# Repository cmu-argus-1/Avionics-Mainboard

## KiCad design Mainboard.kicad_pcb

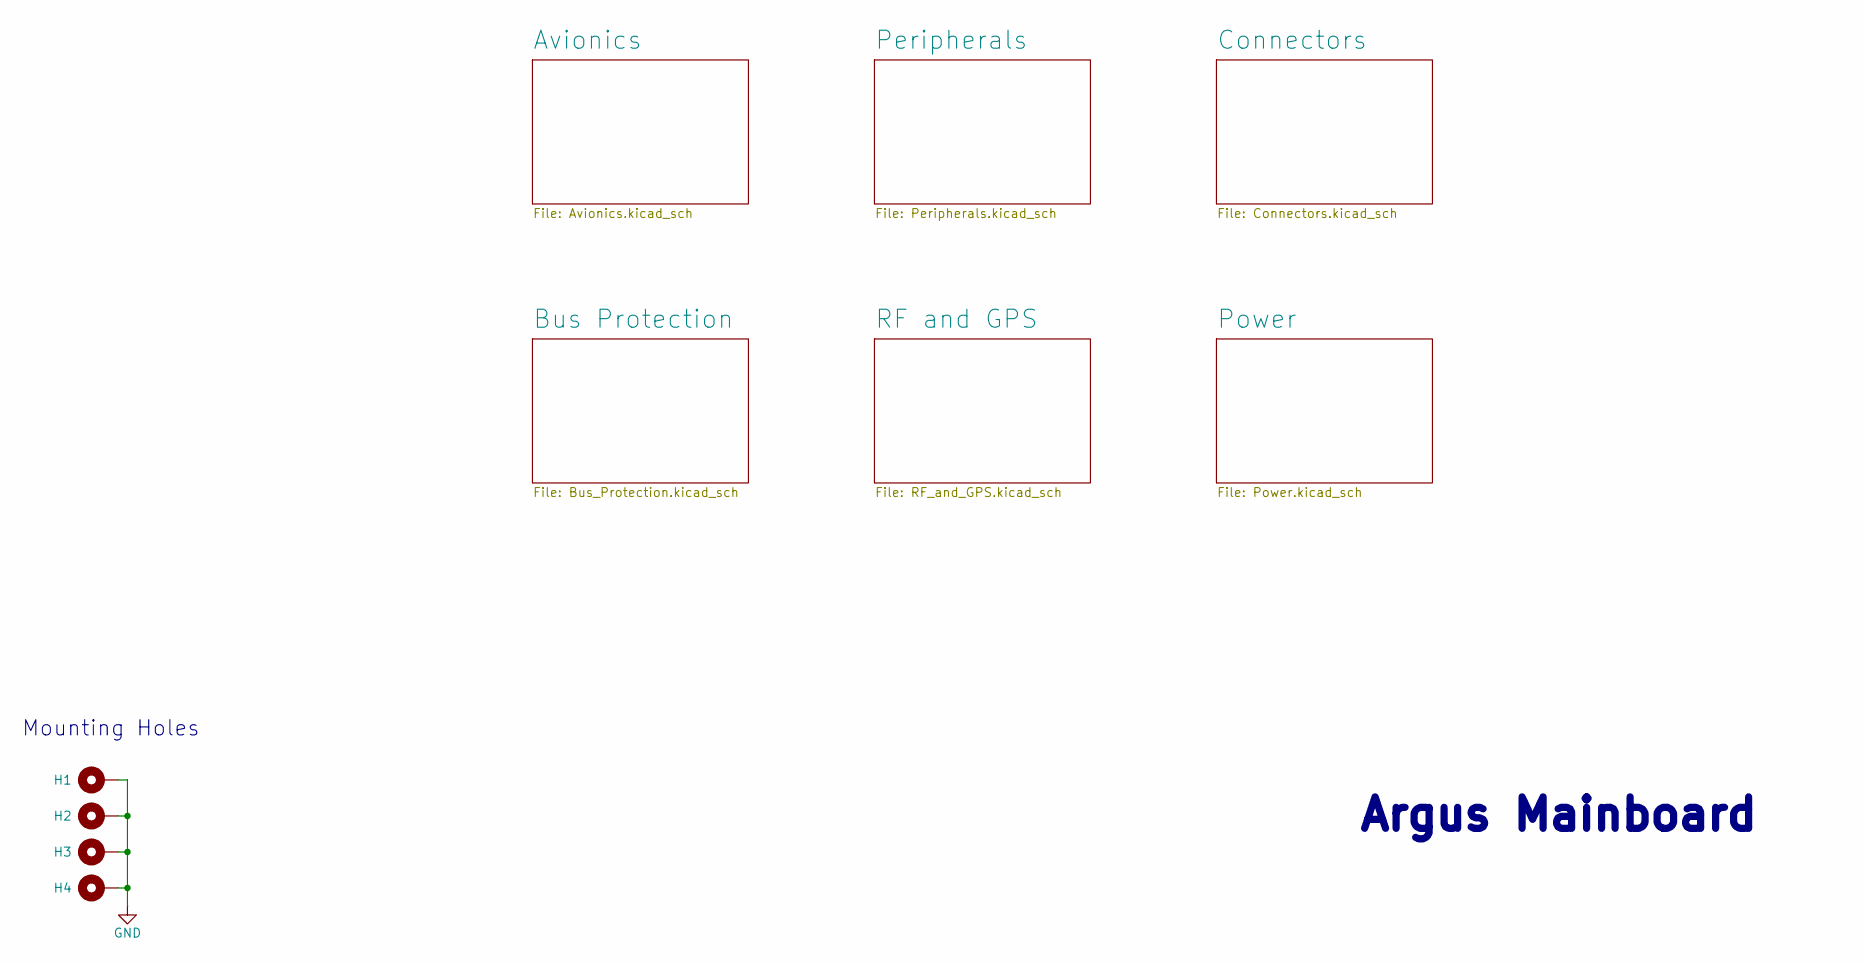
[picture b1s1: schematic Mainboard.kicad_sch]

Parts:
H1, H2, H3, H4: MountingHole_Pad; MountingHole2

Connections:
GND: H1.1, H2.1, H3.1, H4.1; also elsewhere on the board

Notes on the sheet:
Mounting Holes
Argus Mainboard

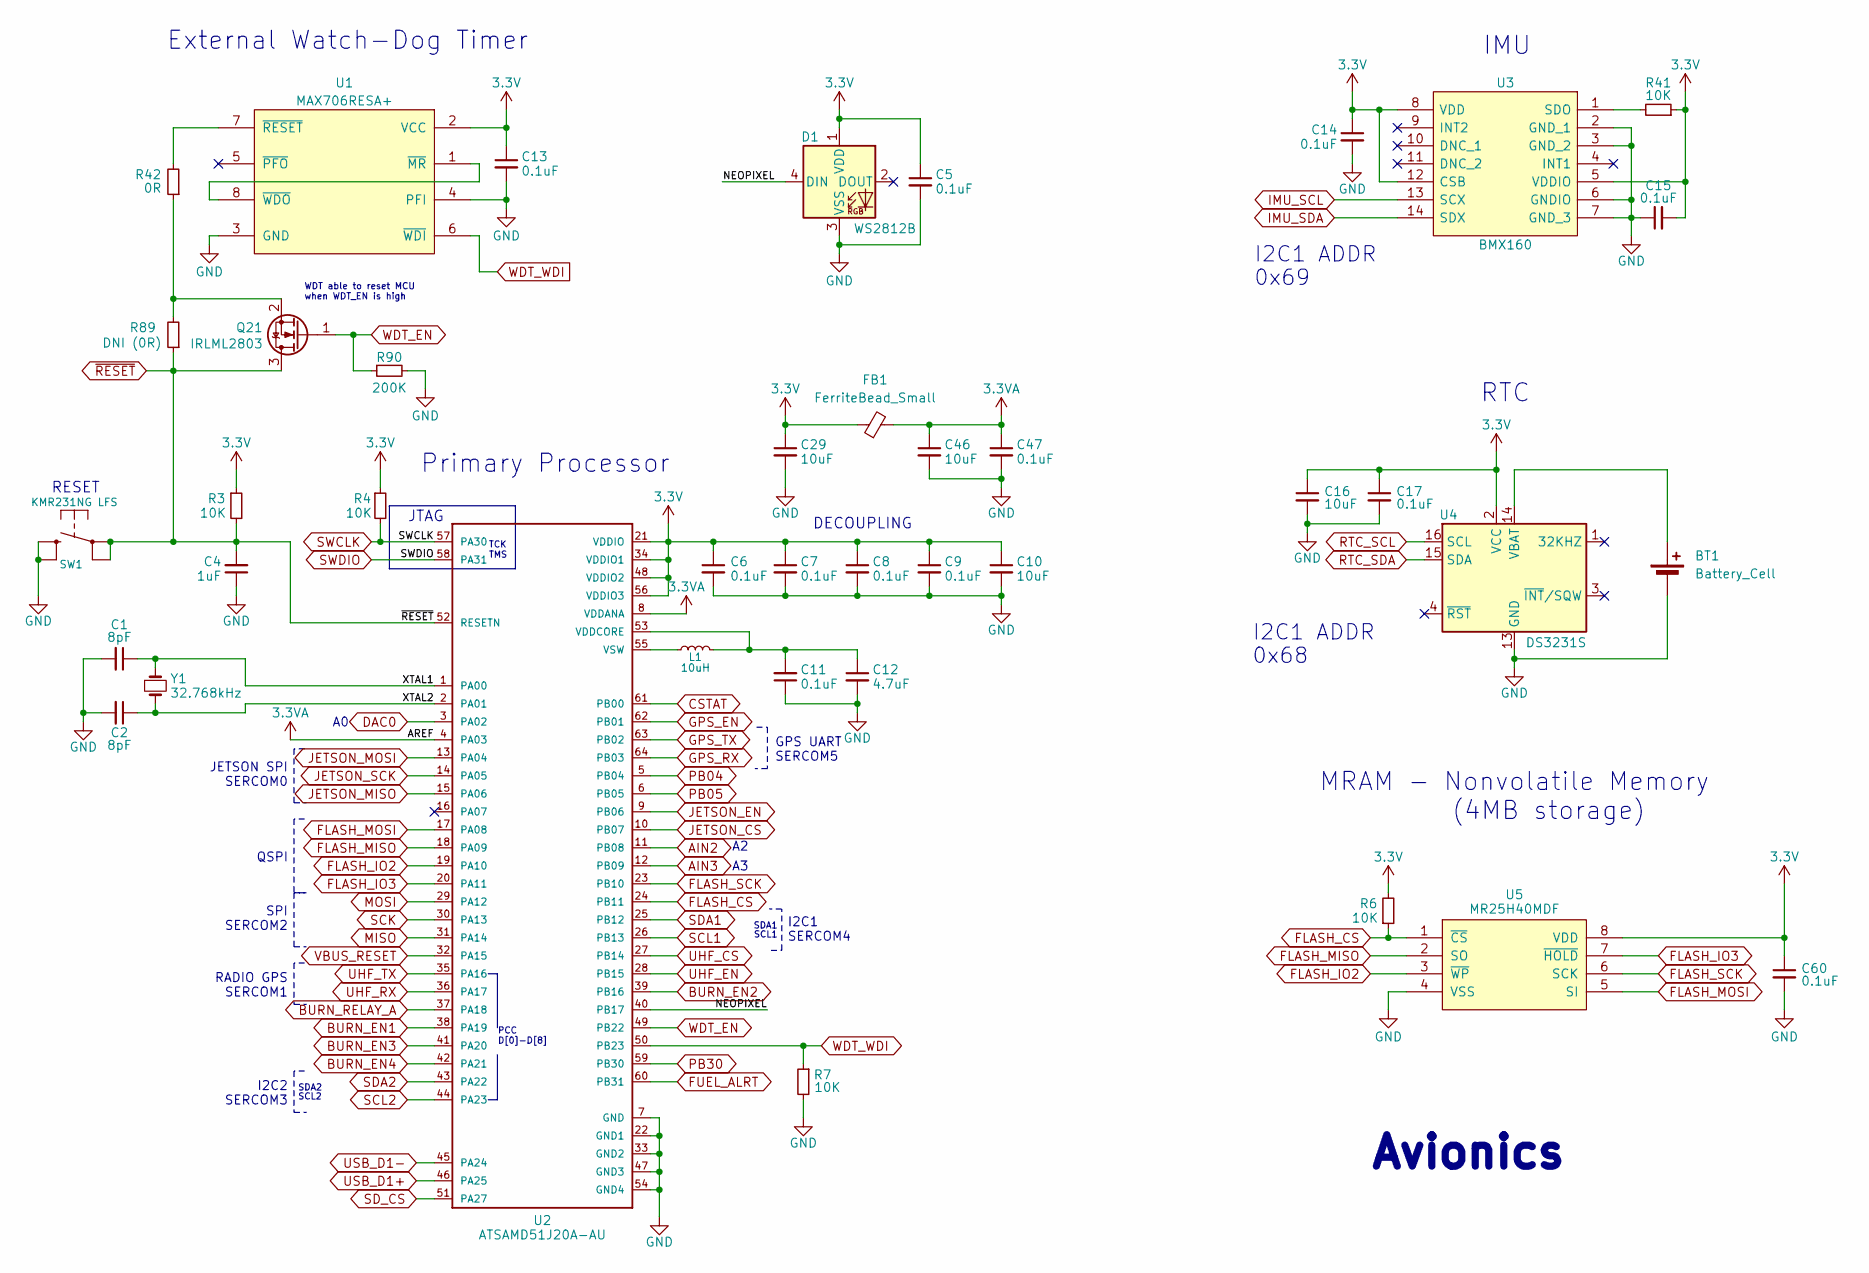
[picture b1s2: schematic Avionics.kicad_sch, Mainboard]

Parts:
BT1: Battery_Cell; BatteryHolder_LINX_BAT-HLD-012-SMT
C1, C2: 8pF; C_0603_1608Metric
C4: 1uF; C_0603_1608Metric
C5, C6, C7, C8, C9, C11, C13, C14, C15, C17, C47, C60: 0.1uF; C_0603_1608Metric
C10, C16, C29, C46: 10uF; C_0603_1608Metric
C12: 4.7uF; C_0603_1608Metric
D1: WS2812B; LED_WS2812B_PLCC4_5.0x5.0mm_P3.2mm; Manufacturer_Part_Number WS2812B-B
FB1: FerriteBead_Small; L_0603_1608Metric
L1: 10uH; L_0805_2012Metric_Pad1.15x1.40mm_HandSolder; Manufacturer_Part_Number MGFL2012F100MT-LF
Q21: IRLML2803; SOT-23
R3, R4, R6, R7, R41: 10K; R_0603_1608Metric
R42: 0R; R_0603_1608Metric
R89: DNI (0R); R_0603_1608Metric
R90: 200K; R_0603_1608Metric
SW1: KMR231NG LFS; SW_Push_1P1T_NO_CK_KMR2; Manufacturer_Part_Number KMR231NG LFS
U1: MAX706RESA+; SOIC-8_3.9x4.9mm_P1.27mm
U2: ATSAMD51J20A-AU; TQFP-64_10x10mm_P0.5mm; Manufacturer_Part_Number ATSAMD51J20A-AU
U3: BMX160; Bosch_LGA-14_3x2.5mm_P0.5mm; Manufacturer_Part_Number BMX160
U4: DS3231S; SOIC-16W_7.5x10.3mm_P1.27mm
U5: MR25H40MDF; DFN-8-1EP_6x5mm_P1.27mm_EP2x2mm; Manufacturer_Part_Number W25Q80DVSNIG
Y1: 32.768kHz; Crystal_SMD_3215-2Pin_3.2x1.5mm; Manufacturer_Part_Number SC-32S32.768kHz20PPM7pF

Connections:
3.3V: C5.1, C6.1, C7.1, C8.1, C9.1, C10.1, C13.1, C14.1, C15.2, C16.1, C17.1, C29.1, C60.1, D1.1 (VDD), FB1.1, R3.1, R4.1, R6.2, R41.1, U1.2 (VCC), U2.21 (VDDIO), U2.34 (VDDIO1), U2.48 (VDDIO2), U2.56 (VDDIO3), U3.5 (VDDIO), U3.8 (VDD), U3.12 (CSB), U4.2 (VCC), U5.8 (VDD); also elsewhere on the board
3.3VA: C46.1, C47.1, FB1.2, U2.4 (PA03), U2.8 (VDDANA)
/Avionics/NEOPIXEL: D1.4 (DIN), U2.40 (PB17)
/Avionics/XTAL1: C1.1, U2.1 (PA00), Y1.1
/Avionics/XTAL2: C2.1, U2.2 (PA01), Y1.2
AIN2: U2.11 (PB08); also elsewhere on the board
AIN3: U2.12 (PB09)
BURN_EN1: U2.38 (PA19); also elsewhere on the board
BURN_EN2: U2.39 (PB16); also elsewhere on the board
BURN_EN3: U2.41 (PA20); also elsewhere on the board
BURN_EN4: U2.42 (PA21); also elsewhere on the board
BURN_RELAY_A: U2.37 (PA18); also elsewhere on the board
CSTAT: U2.61 (PB00); also elsewhere on the board
DAC0: U2.3 (PA02); also elsewhere on the board
FLASH_CS: R6.1, U2.24 (PB11), U5.1 (~CS)
FLASH_IO2: U2.19 (PA10), U5.3 (~WP)
FLASH_IO3: U2.20 (PA11), U5.7 (~HOLD)
FLASH_MISO: U2.18 (PA09), U5.2 (SO)
FLASH_MOSI: U2.17 (PA08), U5.5 (SI)
FLASH_SCK: U2.23 (PB10), U5.6 (SCK)
FUEL_ALRT: U2.60 (PB31); also elsewhere on the board
GND: BT1.2 (-), C1.2, C2.2, C4.1, C5.2, C6.2, C7.2, C8.2, C9.2, C10.2, C11.1, C12.2, C13.2, C14.2, C15.1, C16.2, C17.2, C29.2, C46.2, C47.2, C60.2, D1.3 (VSS), R7.2, R90.2, SW1.2 (S), U1.3 (GND), U1.4 (PFI), U2.7 (GND), U2.22 (GND1), U2.33 (GND2), U2.47 (GND3), U2.54 (GND4), U3.2 (GND_1), U3.3 (GND_2), U3.6 (GNDIO), U3.7 (GND_3), U4.5 (GND), U4.6 (GND), U4.7 (GND), U4.8 (GND), U4.9 (GND), U4.10 (GND), U4.11 (GND), U4.12 (GND), U4.13 (GND), U5.4 (VSS), U5.9 (EP); also elsewhere on the board
GPS_EN: U2.62 (PB01); also elsewhere on the board
GPS_RX: U2.64 (PB03); also elsewhere on the board
GPS_TX: U2.63 (PB02); also elsewhere on the board
IMU_SCL: U3.13 (SCX); also elsewhere on the board
IMU_SDA: U3.14 (SDX); also elsewhere on the board
JETSON_CS: U2.10 (PB07); also elsewhere on the board
JETSON_EN: U2.9 (PB06); also elsewhere on the board
JETSON_MISO: U2.15 (PA06); also elsewhere on the board
JETSON_MOSI: U2.13 (PA04); also elsewhere on the board
JETSON_SCK: U2.14 (PA05); also elsewhere on the board
MISO: U2.31 (PA14); also elsewhere on the board
MOSI: U2.29 (PA12); also elsewhere on the board
unnamed: BT1.1 (+), U4.14 (VBAT)
unnamed: Q21.2 (S), R42.1, R89.2
unnamed: U1.1 (~MR), U1.8 (~WDO)
unnamed: R42.2, U1.7 (~RESET)
unnamed: C11.2, C12.1, L1.1, U2.53 (VDDCORE)
unnamed: L1.2, U2.55 (VSW)
unnamed: R41.2, U3.1 (SDO)
PB04: U2.5 (PB04); also elsewhere on the board
PB05: U2.6 (PB05); also elsewhere on the board
PB30: U2.59 (PB30); also elsewhere on the board
RTC_SCL: U4.16 (SCL); also elsewhere on the board
RTC_SDA: U4.15 (SDA); also elsewhere on the board
SCK: U2.30 (PA13); also elsewhere on the board
SCL1: U2.26 (PB13); also elsewhere on the board
SCL2: U2.44 (PA23); also elsewhere on the board
SDA1: U2.25 (PB12); also elsewhere on the board
SDA2: U2.43 (PA22); also elsewhere on the board
SD_CS: U2.51 (PA27); also elsewhere on the board
SWCLK: R4.2, U2.57 (PA30); also elsewhere on the board
SWDIO: U2.58 (PA31); also elsewhere on the board
UHF_CS: U2.27 (PB14); also elsewhere on the board
UHF_EN: U2.28 (PB15); also elsewhere on the board
UHF_RX: U2.36 (PA17); also elsewhere on the board
UHF_TX: U2.35 (PA16); also elsewhere on the board
USB_D1+: U2.46 (PA25); also elsewhere on the board
USB_D1-: U2.45 (PA24); also elsewhere on the board
VBUS_RESET: U2.32 (PA15); also elsewhere on the board
WDT_EN: Q21.1 (G), R90.1, U2.49 (PB22)
WDT_WDI: R7.1, U1.6 (~WDI), U2.50 (PB23)
~RESET: C4.2, Q21.3 (D), R3.2, R89.1, SW1.1, U2.52 (RESETN); also elsewhere on the board

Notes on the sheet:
RTC
RADIO GPS SERCOM1
SDA2
Primary Processor
SCL2
I2C1 ADDR
0x69
GPS UART SERCOM5
IMU
I2C1 SERCOM4
SPI SERCOM2
RESET
WDT able to reset MCU when WDT_EN is high
JETSON SPI SERCOM0
0x68
Avionics
SDA1
SCL1
TCK TMS
QSPI
External Watch-Dog Timer
I2C2 SERCOM3
PCC D[0]-D[8]
JTAG
DECOUPLING
MRAM - Nonvolatile Memory (4MB storage)

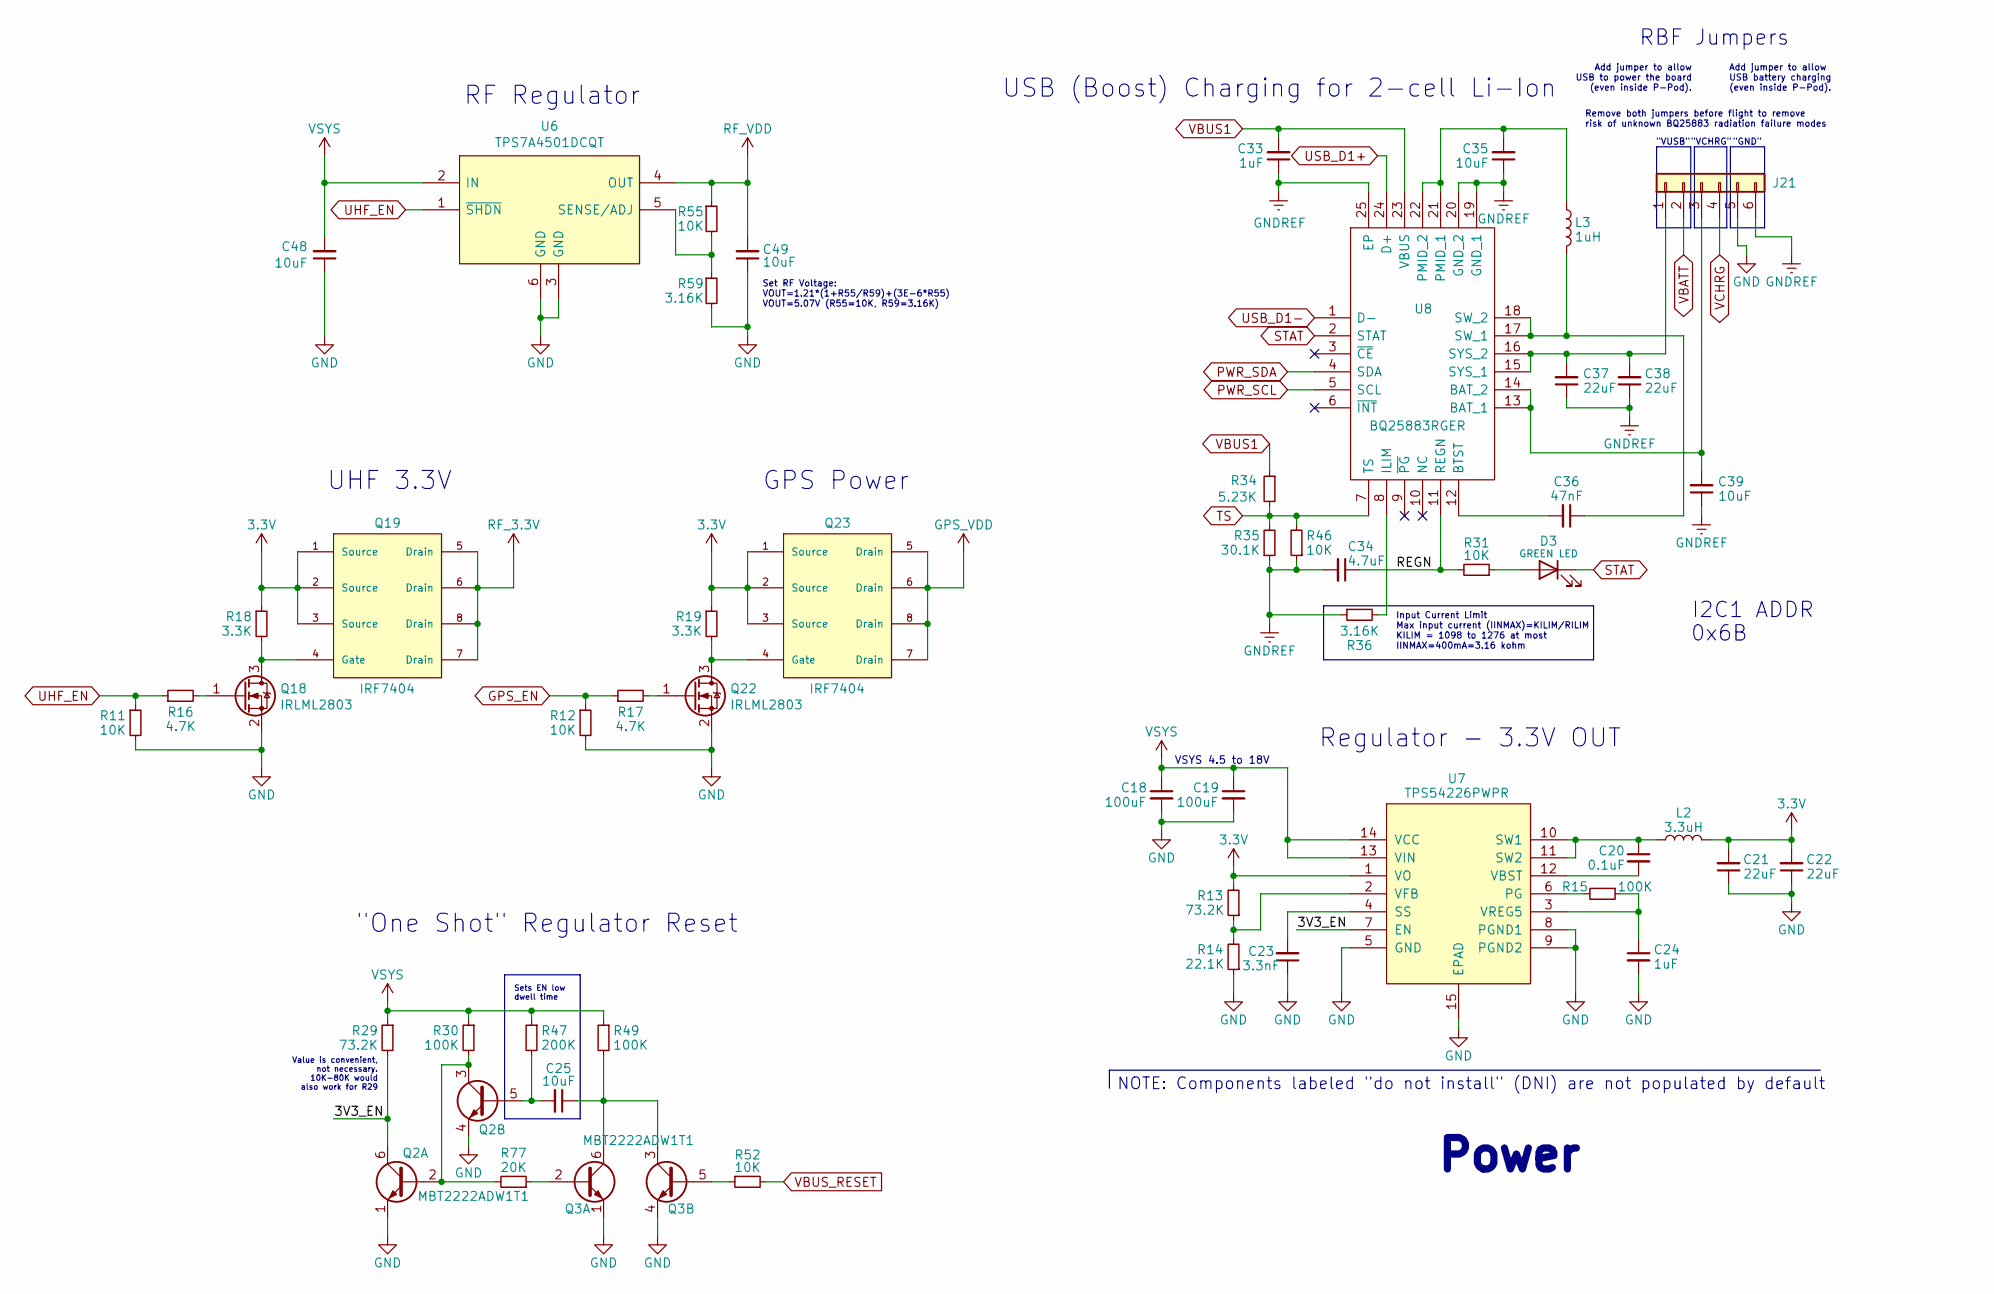
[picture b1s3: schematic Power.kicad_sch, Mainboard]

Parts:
C18, C19: 100uF; C_0805_2012Metric
C20: 0.1uF; C_0603_1608Metric
C21, C22, C37, C38: 22uF; C_0603_1608Metric
C23: 3.3nF; C_0603_1608Metric
C24, C33: 1uF; C_0603_1608Metric
C25, C35, C39, C48, C49: 10uF; C_0603_1608Metric
C34: 4.7uF; C_0603_1608Metric
C36: 47nF; C_0603_1608Metric
D3: GREEN LED; LED_0603_1608Metric; Manufacturer_Part_Number LTST-C190KGKT
J21: Conn_01x06; PinHeader_1x06_P2.54mm_Vertical
L2: 3.3uH; L_1812_4532Metric; Manufacturer_Part_Number HPC5040NF-3R3MTH
L3: 1uH; L_Wuerth_MAPI-2510; Manufacturer_Part_Number MCS25GD-1R0MMP
Q2, Q3: MBT2222ADW1T1; SOT-363_SC-70-6; Manufacturer_Part_Number MBT2222ADW1T1G
Q18, Q22: IRLML2803; SOT-23
Q19, Q23: IRF7404; SOIC-8_3.9x4.9mm_P1.27mm; Manufacturer_Part_Number NDS8434
R11, R12, R31, R46, R52, R55: 10K; R_0603_1608Metric
R13, R29: 73.2K; R_0603_1608Metric
R14: 22.1K; R_0603_1608Metric
R15, R30, R49: 100K; R_0603_1608Metric
R16, R17: 4.7K; R_0603_1608Metric
R18, R19: 3.3K; R_0603_1608Metric
R34: 5.23K; R_0603_1608Metric
R35: 30.1K; R_0603_1608Metric
R36, R59: 3.16K; R_0603_1608Metric
R47: 200K; R_0603_1608Metric
R77: 20K; R_0603_1608Metric
U6: TPS7A4501DCQT; SOT-223-6; Manufacturer_Part_Number TPS7A4501DCQT
U7: TPS54226PWPR; HTSSOP-14-1EP_4.4x5mm_P0.65mm_EP3.4x5mm_Mask3x3.1mm; Manufacturer_Part_Number TPS54226PWPR
U8: BQ25883RGER; Texas_RGE0024H_VQFN-24-1EP_4x4mm_P0.5mm_EP2.7x2.7mm; Manufacturer_Part_Number BQ25883RGER

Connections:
3.3V: C21.2, C22.2, L2.2, Q19.1 (Source), Q19.2 (Source), Q19.3 (Source), Q23.1 (Source), Q23.2 (Source), Q23.3 (Source), R13.2, R18.1, R19.1, U7.1 (VO); also elsewhere on the board
/Power/3V3_EN: Q2.6 (C1), R29.2, U7.7 (EN)
/Power/REGN: C34.1, R31.2, U8.11 (REGN)
GND: C18.2, C19.2, C21.1, C22.1, C23.1, C24.2, C48.1, C49.1, J21.5, Q2.1 (E1), Q2.4 (E2), Q3.1 (E1), Q3.4 (E2), Q18.2 (S), Q22.2 (S), R11.2, R12.2, R14.1, R59.2, U6.3 (GND), U6.6 (GND), U7.5 (GND), U7.8 (PGND1), U7.9 (PGND2), U7.15 (EPAD); also elsewhere on the board
GNDREF: C33.1, C34.2, C35.1, C37.1, C38.1, C39.1, J21.6, R35.1, R36.1, R46.1, U8.19 (GND_1), U8.20 (GND_2), U8.25 (EP); also elsewhere on the board
GPS_EN: R12.1, R17.1; also elsewhere on the board
GPS_VDD: Q23.5 (Drain), Q23.6 (Drain), Q23.7 (Drain), Q23.8 (Drain); also elsewhere on the board
unnamed: D3.2 (A), R31.1
unnamed: C37.2, C38.2, J21.1, U8.15 (SYS_1), U8.16 (SYS_2)
unnamed: C39.2, J21.3, U8.13 (BAT_1), U8.14 (BAT_2)
unnamed: Q2.2 (B1), Q2.3 (C2), R30.2, R77.2
unnamed: C25.2, Q2.5 (B2), R47.2
unnamed: Q3.2 (B1), R77.1
unnamed: C25.1, Q3.3 (C2), Q3.6 (C1), R49.2
unnamed: Q3.5 (B2), R52.1
unnamed: Q18.3 (D), Q19.4 (Gate), R18.2
unnamed: Q18.1 (G), R16.2
unnamed: Q22.3 (D), Q23.4 (Gate), R19.2
unnamed: Q22.1 (G), R17.2
unnamed: R55.2, R59.1, U6.5 (SENSE/ADJ)
unnamed: R15.2, U7.6 (PG)
unnamed: C23.2, U7.4 (SS)
unnamed: C20.1, L2.1, U7.10 (SW1), U7.11 (SW2)
unnamed: C20.2, U7.12 (VBST)
unnamed: R13.1, R14.2, U7.2 (VFB)
unnamed: C24.1, R15.1, U7.3 (VREG5)
unnamed: C36.2, U8.12 (BTST)
unnamed: R36.2, U8.8 (ILIM)
unnamed: C35.2, L3.1, U8.21 (PMID_1), U8.22 (PMID_2)
unnamed: C36.1, L3.2, U8.17 (SW_1), U8.18 (SW_2)
PWR_SCL: U8.5 (SCL); also elsewhere on the board
PWR_SDA: U8.4 (SDA); also elsewhere on the board
RF_3.3V: Q19.5 (Drain), Q19.6 (Drain), Q19.7 (Drain), Q19.8 (Drain); also elsewhere on the board
RF_VDD: C49.2, R55.1, U6.4 (OUT); also elsewhere on the board
STAT: D3.1 (K), U8.2 (STAT)
TS: R34.2, R35.2, R46.2, U8.7 (TS)
UHF_EN: R11.1, R16.1, U6.1 (~SHDN); also elsewhere on the board
USB_D1+: U8.24 (D+); also elsewhere on the board
USB_D1-: U8.1 (D-); also elsewhere on the board
VBATT: J21.2; also elsewhere on the board
VBUS1: C33.2, R34.1, U8.23 (VBUS); also elsewhere on the board
VBUS_RESET: R52.2; also elsewhere on the board
VCHRG: J21.4; also elsewhere on the board
VSYS: C18.1, C19.1, C48.2, R29.1, R30.1, R47.1, R49.1, U6.2 (IN), U7.13 (VIN), U7.14 (VCC); also elsewhere on the board

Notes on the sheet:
"VCHRG"
RF Regulator
Sets EN low dwell time
Remove both jumpers before flight to remove risk of unknown BQ25883 radiation failure modes
0x6B
RBF Jumpers
Add jumper to allow USB battery charging (even inside P-Pod).
"One Shot" Regulator Reset
GPS Power
Value is convenient, not necessary. 10K-80K would also work for R29
USB (Boost) Charging for 2-cell Li-Ion
UHF 3.3V
"GND"
VSYS 4.5 to 18V
Input Current Limit Max input current (IINMAX)=KILIM/RILIM KILIM = 1098 to 1276 at most IINMAX=400mA=3.16 kohm
"VUSB"
I2C1 ADDR
Power
Set RF Voltage: VOUT=1.21*(1+R55/R59)+(3E-6*R55) VOUT=5.07V (R55=10K, R59=3.16K)
Regulator - 3.3V OUT
Add jumper to allow USB to power the board (even inside P-Pod).
NOTE: Components labeled "do not install" (DNI) are not populated by default

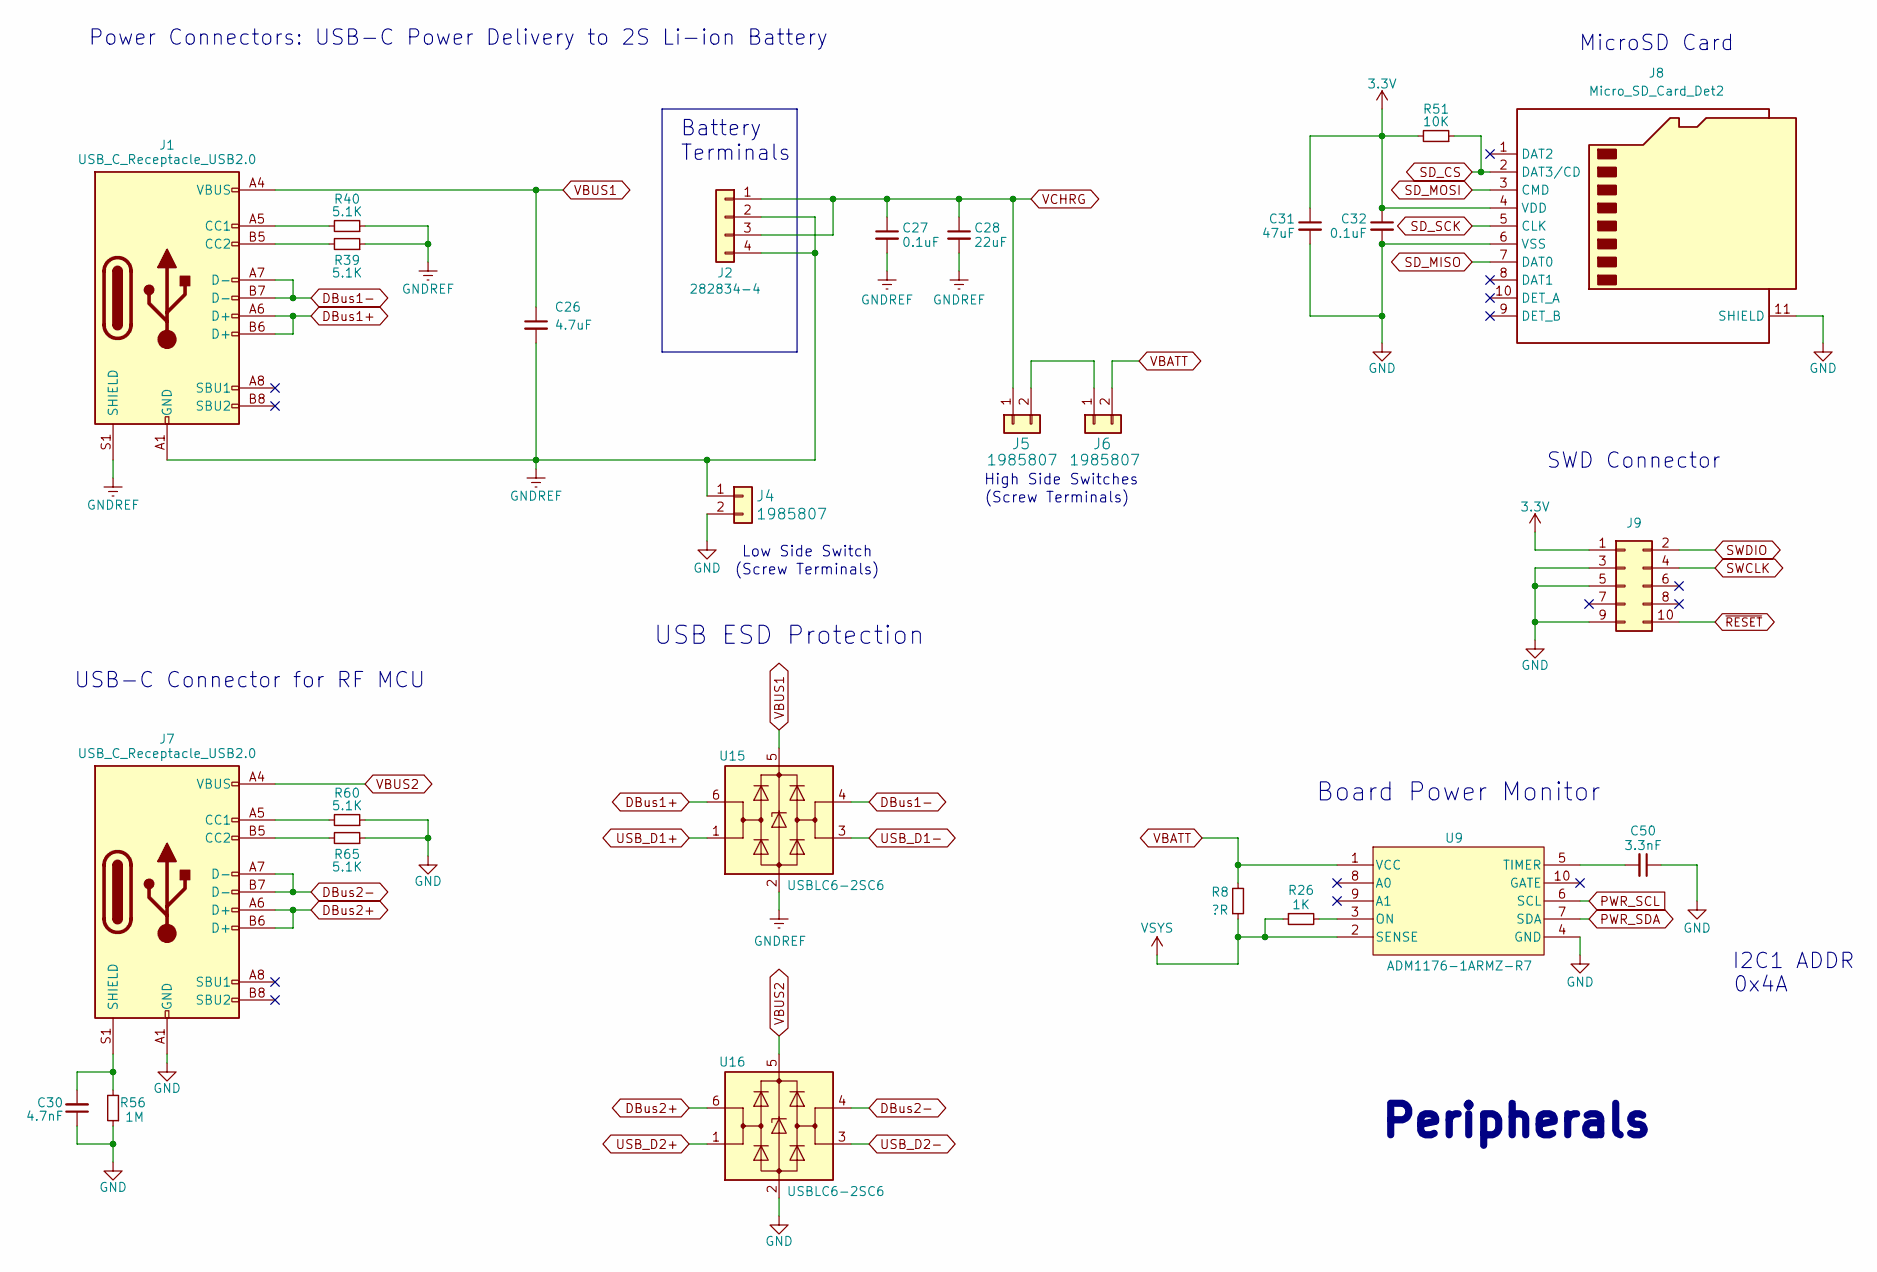
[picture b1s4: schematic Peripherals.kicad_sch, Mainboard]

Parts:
C26: 4.7uF; C_0603_1608Metric
C27, C32: 0.1uF; C_0603_1608Metric
C28: 22uF; C_0603_1608Metric
C30: 4.7nF; C_0603_1608Metric
C31: 47uF; C_0805_2012Metric
C50: 3.3nF; C_0603_1608Metric
J1, J7: USB_C_Receptacle_USB2.0; USB_C_Receptacle_HRO_TYPE-C-31-M-12; Manufacturer_Part_Number U262-161N-4BVC11
J2: 282834-4; TE_282834-4
J4, J5, J6: 1985807; PHOENIX_1985807; Manufacturer_Part_Number 1985807
J8: Micro_SD_Card_Det2; microSD_HC_Molex_104031-0811
J9: Conn_02x05_Odd_Even; PinHeader_2x05_P1.27mm_Vertical_SMD
R8: ?R; R_2512_6332Metric
R26: 1K; R_0603_1608Metric
R39, R40, R60, R65: 5.1K; R_0603_1608Metric
R51: 10K; R_0603_1608Metric
R56: 1M; R_0603_1608Metric
U9: ADM1176-1ARMZ-R7; MSOP-10_3x3mm_P0.5mm; Manufacturer_Part_Number ADM1176-1ARMZ-R7
U15, U16: USBLC6-2SC6; SOT-23-6

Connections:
3.3V: C31.1, C32.1, J8.4 (VDD), J9.1, R51.2; also elsewhere on the board
DBus1+: J1.A6 (D+), J1.B6 (D+), U15.6 (I/O1)
DBus1-: J1.A7 (D-), J1.B7 (D-), U15.4 (I/O2)
DBus2+: J7.A6 (D+), J7.B6 (D+), U16.6 (I/O1)
DBus2-: J7.A7 (D-), J7.B7 (D-), U16.4 (I/O2)
GND: C30.1, C31.2, C32.2, C50.1, J4.2, J7.A1 (GND), J7.A12 (GND), J7.B1 (GND), J7.B12 (GND), J8.6 (VSS), J8.11 (SHIELD), J9.3, J9.5, J9.9, R56.1, R60.1, R65.1, U9.4 (GND), U16.2 (GND); also elsewhere on the board
GNDREF: C26.2, C27.2, C28.2, J1.A1 (GND), J1.A12 (GND), J1.B1 (GND), J1.B12 (GND), J1.S1 (SHIELD), J2.2, J2.4, J4.1, R39.1, R40.1, U15.2 (GND); also elsewhere on the board
unnamed: J1.A5 (CC1), R40.2
unnamed: J1.B5 (CC2), R39.2
unnamed: J5.2, J6.1
unnamed: J7.A5 (CC1), R60.2
unnamed: J7.B5 (CC2), R65.2
unnamed: C30.2, J7.S1 (SHIELD), R56.2
unnamed: R26.2, U9.3 (ON)
unnamed: C50.2, U9.5 (TIMER)
PWR_SCL: U9.6 (SCL); also elsewhere on the board
PWR_SDA: U9.7 (SDA); also elsewhere on the board
SD_CS: J8.2 (DAT3/CD), R51.1; also elsewhere on the board
SD_MISO: J8.7 (DAT0); also elsewhere on the board
SD_MOSI: J8.3 (CMD); also elsewhere on the board
SD_SCK: J8.5 (CLK); also elsewhere on the board
SWCLK: J9.4; also elsewhere on the board
SWDIO: J9.2; also elsewhere on the board
USB_D1+: U15.1 (I/O1); also elsewhere on the board
USB_D1-: U15.3 (I/O2); also elsewhere on the board
USB_D2+: U16.1 (I/O1); also elsewhere on the board
USB_D2-: U16.3 (I/O2); also elsewhere on the board
VBATT: J6.2, R8.2, U9.1 (VCC); also elsewhere on the board
VBUS1: C26.1, J1.A4 (VBUS), J1.A9 (VBUS), J1.B4 (VBUS), J1.B9 (VBUS), U15.5 (VBUS); also elsewhere on the board
VBUS2: J7.A4 (VBUS), J7.A9 (VBUS), J7.B4 (VBUS), J7.B9 (VBUS), U16.5 (VBUS)
VCHRG: C27.1, C28.1, J2.1, J2.3, J5.1; also elsewhere on the board
VSYS: R8.1, R26.1, U9.2 (SENSE); also elsewhere on the board
~RESET: J9.10; also elsewhere on the board

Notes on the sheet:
Power Connectors: USB-C Power Delivery to 2S Li-ion Battery
(Screw Terminals)
0x4A
SWD Connector
MicroSD Card
Low Side Switch
Board Power Monitor
Peripherals
I2C1 ADDR
USB ESD Protection
Battery Terminals
USB-C Connector for RF MCU
High Side Switches

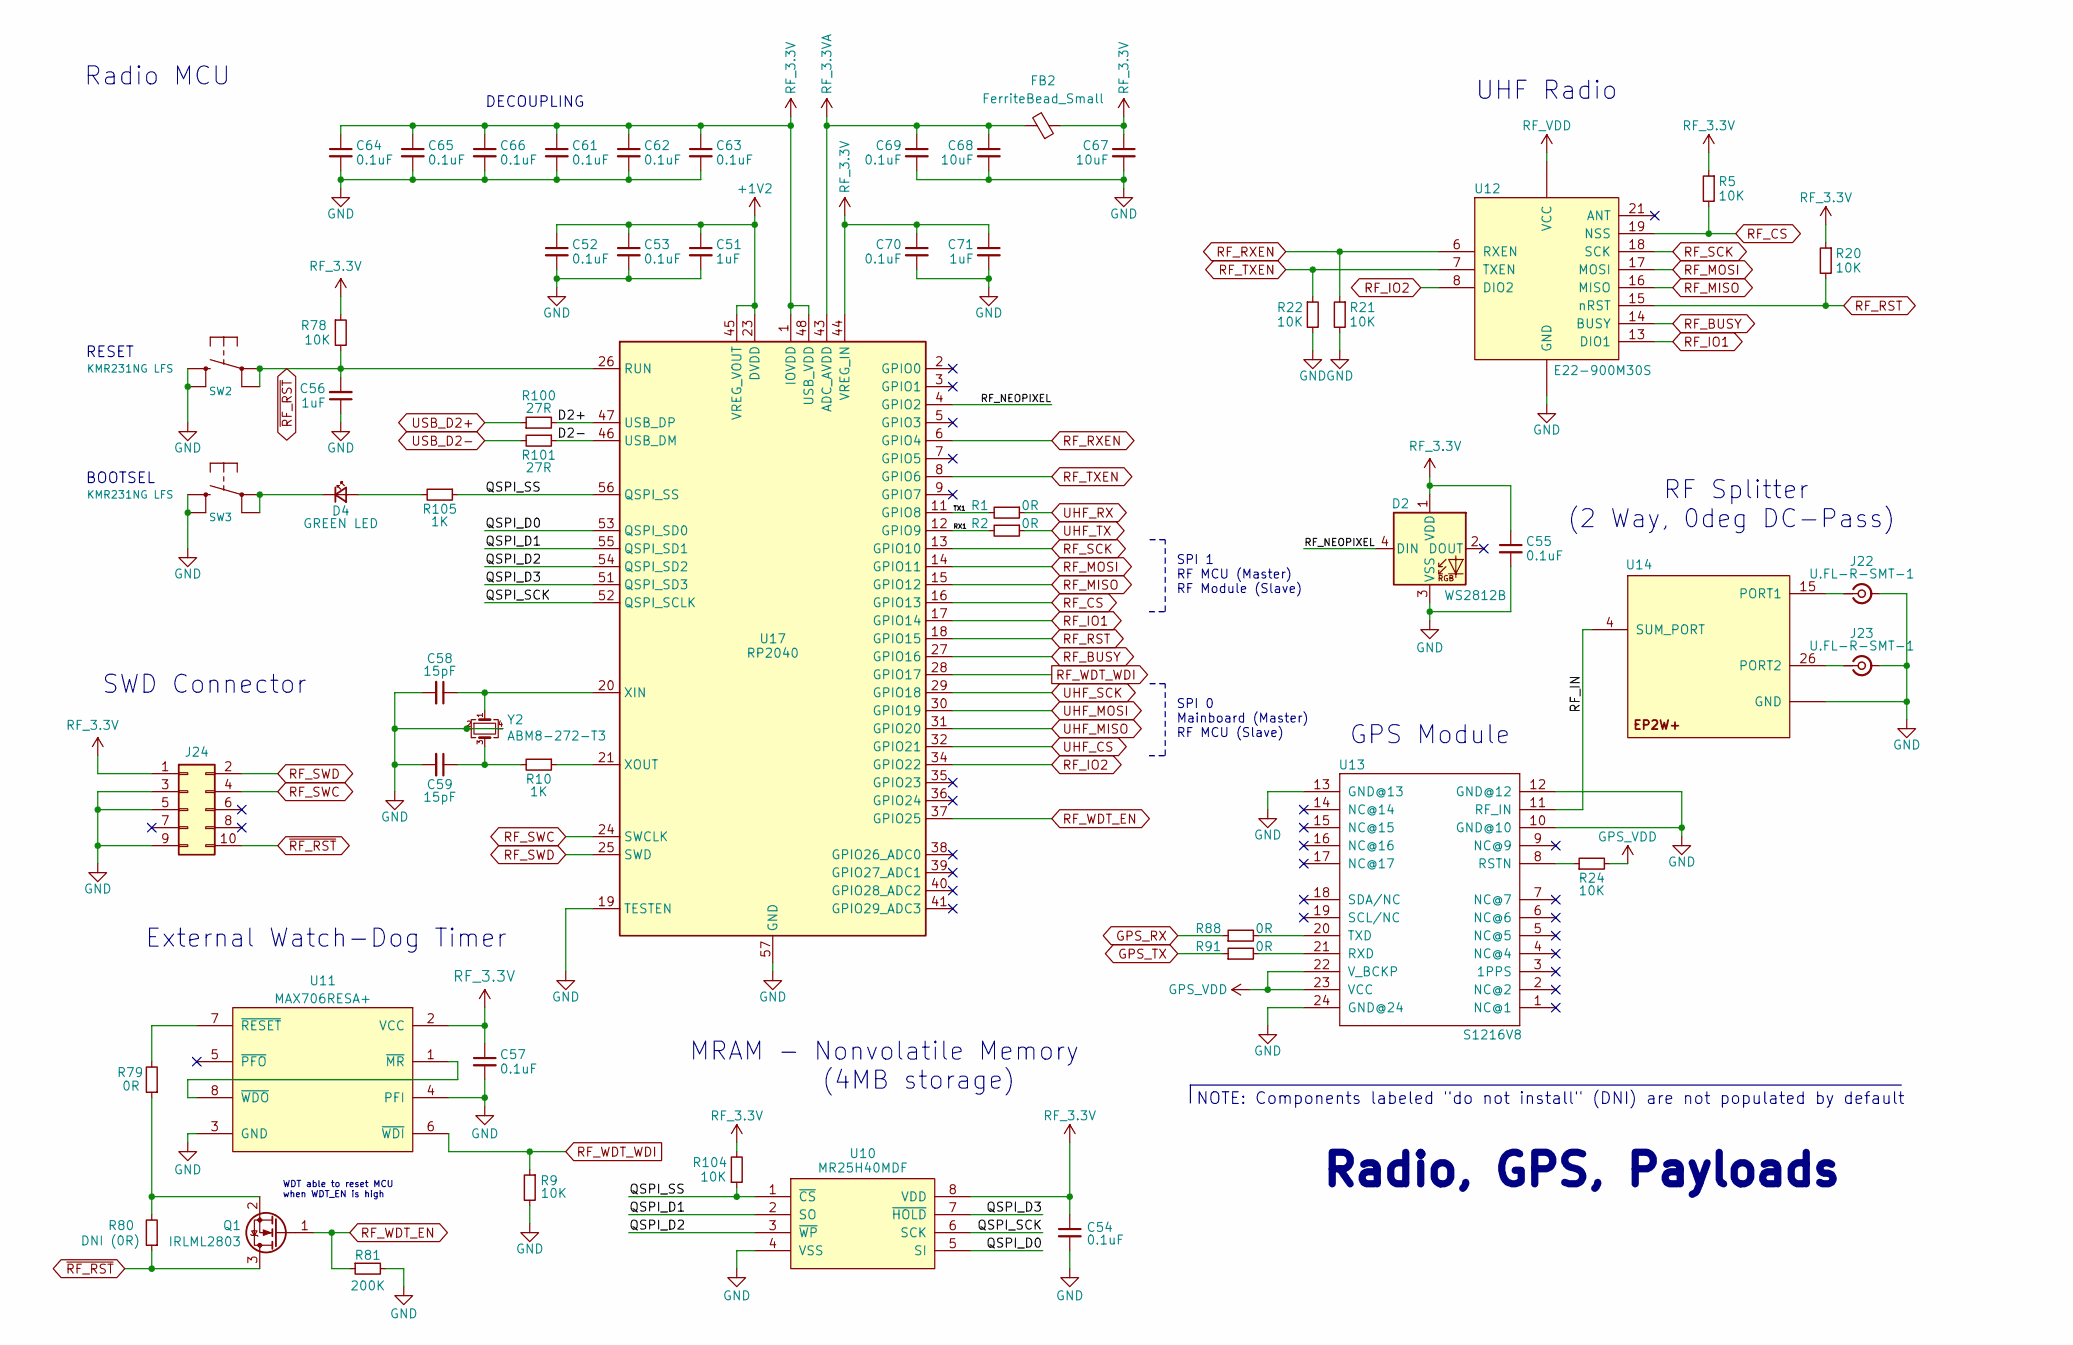
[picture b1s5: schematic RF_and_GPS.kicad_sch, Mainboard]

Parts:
C51, C56, C71: 1uF; C_0603_1608Metric
C52, C53, C54, C55, C57, C61, C62, C63, C64, C65, C66, C69, C70: 0.1uF; C_0603_1608Metric
C58, C59: 15pF; C_0603_1608Metric
C67, C68: 10uF; C_0603_1608Metric
D2: WS2812B; LED_WS2812B_PLCC4_5.0x5.0mm_P3.2mm; Manufacturer_Part_Number WS2812B-B
D4: GREEN LED; LED_0603_1608Metric
FB2: FerriteBead_Small; L_0603_1608Metric
J22, J23: U.FL-R-SMT-1; U.FL_Hirose_U.FL-R-SMT-1_Vertical
J24: Conn_02x05_Odd_Even; PinHeader_2x05_P1.27mm_Vertical_SMD
Q1: IRLML2803; SOT-23
R1, R2, R79, R88, R91: 0R; R_0603_1608Metric
R5, R9, R20, R21, R22, R24, R78, R104: 10K; R_0603_1608Metric
R10, R105: 1K; R_0603_1608Metric
R80: DNI (0R); R_0603_1608Metric
R81: 200K; R_0603_1608Metric
R100, R101: 27R; R_0603_1608Metric
SW2, SW3: KMR231NG LFS; SW_Push_1P1T_NO_CK_KMR2; Manufacturer_Part_Number KMR231NG LFS
U10: MR25H40MDF; DFN-8-1EP_6x5mm_P1.27mm_EP2x2mm; Manufacturer_Part_Number W25Q80DVSNIG
U11: MAX706RESA+; SOIC-8_3.9x4.9mm_P1.27mm
U12: E22-900M30S; XCVR_E22-900M30S; Manufacturer_Part_Number RFM98PW
U13: S1216V8; S1216_24PIN_PACKAGE
U14: EP2W+; Manufacturer_Part_Number EP2W+
U17: RP2040; QFN-56-1EP_7x7mm_P0.4mm_EP3.2x3.2mm
Y2: ABM8-272-T3; Crystal_SMD_3225-4Pin_3.2x2.5mm

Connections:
+1V2: C51.1, C52.1, C53.1, U17.23 (DVDD), U17.45 (VREG_VOUT), U17.50 (DVDD)
/RF and GPS/D2+: R100.2, U17.47 (USB_DP)
/RF and GPS/D2-: R101.1, U17.46 (USB_DM)
/RF and GPS/QSPI_D0: U10.5 (SI), U17.53 (QSPI_SD0)
/RF and GPS/QSPI_D1: U10.2 (SO), U17.55 (QSPI_SD1)
/RF and GPS/QSPI_D2: U10.3 (~WP), U17.54 (QSPI_SD2)
/RF and GPS/QSPI_D3: U10.7 (~HOLD), U17.51 (QSPI_SD3)
/RF and GPS/QSPI_SCK: U10.6 (SCK), U17.52 (QSPI_SCLK)
/RF and GPS/QSPI_SS: R104.1, R105.1, U10.1 (~CS), U17.56 (QSPI_SS)
/RF and GPS/RF_IN: U13.11 (RF_IN), U14.4 (SUM_PORT)
/RF and GPS/RF_NEOPIXEL: D2.4 (DIN), U17.4 (GPIO2)
/RF and GPS/RX1: R2.2, U17.12 (GPIO9)
/RF and GPS/TX1: R1.2, U17.11 (GPIO8)
GND: C51.2, C52.2, C53.2, C54.2, C55.2, C56.1, C57.2, C58.2, C59.2, C61.2, C62.2, C63.2, C64.2, C65.2, C66.2, C67.2, C68.2, C69.2, C70.2, C71.2, D2.3 (VSS), J22.2 (Ext), J23.2 (Ext), J24.3, J24.5, J24.9, R9.2, R21.2, R22.2, R81.2, SW2.2 (S1), SW3.2 (S), U10.4 (VSS), U10.9 (EP), U11.3 (GND), U11.4 (PFI), U12.1 (GND), U12.2 (GND), U12.3 (GND), U12.4 (GND), U12.5 (GND), U12.11 (GND), U12.12 (GND), U12.20 (GND), U12.22 (GND), U13.10 (GND@10), U13.12 (GND@12), U13.13 (GND@13), U13.24 (GND@24), U14.1 (GND), U14.2 (GND), U14.3 (GND), U14.5 (GND), U14.6 (GND), U14.7 (GND), U14.8 (GND), U14.9 (GND), U14.10 (GND), U14.11 (GND), U14.12 (GND), U14.13 (GND), U14.14 (GND), U14.16 (GND), U14.17 (GND), U14.18 (GND), U14.19 (GND), U14.20 (GND), U14.21 (GND), U14.22 (GND), U14.23 (GND), U14.24 (GND), U14.25 (GND), U14.27 (GND), U14.28 (GND), U14.29 (GND), U14.30 (GND), U14.31 (GND), U14.32 (GND), U14.EP (GND), U17.19 (TESTEN), U17.57 (GND), Y2.2, Y2.4; also elsewhere on the board
GPS_RX: R88.1; also elsewhere on the board
GPS_TX: R91.1; also elsewhere on the board
GPS_VDD: R24.2, U13.22 (V_BCKP), U13.23 (VCC); also elsewhere on the board
unnamed: C59.1, R10.2, Y2.3
unnamed: D4.2 (A), R105.2
unnamed: D4.1 (K), SW3.1
unnamed: J22.1 (In), U14.15 (PORT1)
unnamed: J23.1 (In), U14.26 (PORT2)
unnamed: Q1.2 (S), R79.1, R80.2
unnamed: U11.1 (~MR), U11.8 (~WDO)
unnamed: R79.2, U11.7 (~RESET)
unnamed: R24.1, U13.8 (RSTN)
unnamed: R91.2, U13.21 (RXD)
unnamed: R88.2, U13.20 (TXD)
unnamed: C58.1, U17.20 (XIN), Y2.1
unnamed: R10.1, U17.21 (XOUT)
RF_3.3V: C54.1, C55.1, C57.1, C61.1, C62.1, C63.1, C64.1, C65.1, C66.1, C67.1, C70.1, C71.1, D2.1 (VDD), FB2.1, J24.1, R5.1, R20.1, R78.1, R104.2, U10.8 (VDD), U11.2 (VCC), U17.1 (IOVDD), U17.10 (IOVDD), U17.22 (IOVDD), U17.33 (IOVDD), U17.42 (IOVDD), U17.44 (VREG_IN), U17.48 (USB_VDD), U17.49 (IOVDD); also elsewhere on the board
RF_3.3VA: C68.1, C69.1, FB2.2, U17.43 (ADC_AVDD)
RF_BUSY: U12.14 (BUSY), U17.27 (GPIO16)
RF_CS: R5.2, U12.19 (NSS), U17.16 (GPIO13)
RF_IO1: U12.13 (DIO1), U17.17 (GPIO14)
RF_IO2: U12.8 (DIO2), U17.34 (GPIO22)
RF_MISO: U12.16 (MISO), U17.15 (GPIO12)
RF_MOSI: U12.17 (MOSI), U17.14 (GPIO11)
RF_RST: R20.2, U12.15 (nRST), U17.18 (GPIO15)
RF_RXEN: R21.1, U12.6 (RXEN), U17.6 (GPIO4)
RF_SCK: U12.18 (SCK), U17.13 (GPIO10)
RF_SWC: J24.4, U17.24 (SWCLK)
RF_SWD: J24.2, U17.25 (SWD)
RF_TXEN: R22.1, U12.7 (TXEN), U17.8 (GPIO6)
RF_VDD: U12.9 (VCC), U12.10 (VCC); also elsewhere on the board
RF_WDT_EN: Q1.1 (G), R81.1, U17.37 (GPIO25)
RF_WDT_WDI: R9.1, U11.6 (~WDI), U17.28 (GPIO17)
UHF_CS: U17.32 (GPIO21); also elsewhere on the board
UHF_MISO: U17.31 (GPIO20); also elsewhere on the board
UHF_MOSI: U17.30 (GPIO19); also elsewhere on the board
UHF_RX: R1.1; also elsewhere on the board
UHF_SCK: U17.29 (GPIO18); also elsewhere on the board
UHF_TX: R2.1; also elsewhere on the board
USB_D2+: R100.1; also elsewhere on the board
USB_D2-: R101.2; also elsewhere on the board
~RF_RST: C56.2, J24.10, Q1.3 (D), R78.2, R80.1, SW2.1, U17.26 (RUN)

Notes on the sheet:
Radio, GPS, Payloads
External Watch-Dog Timer
SWD Connector
SPI 1 RF MCU (Master) RF Module (Slave)
RF Splitter (2 Way, 0deg DC-Pass)
SPI 0 Mainboard (Master) RF MCU (Slave)
NOTE: Components labeled "do not install" (DNI) are not populated by default
Radio MCU
GPS Module
RESET
DECOUPLING
BOOTSEL
UHF Radio
MRAM - Nonvolatile Memory (4MB storage)
WDT able to reset MCU when WDT_EN is high
